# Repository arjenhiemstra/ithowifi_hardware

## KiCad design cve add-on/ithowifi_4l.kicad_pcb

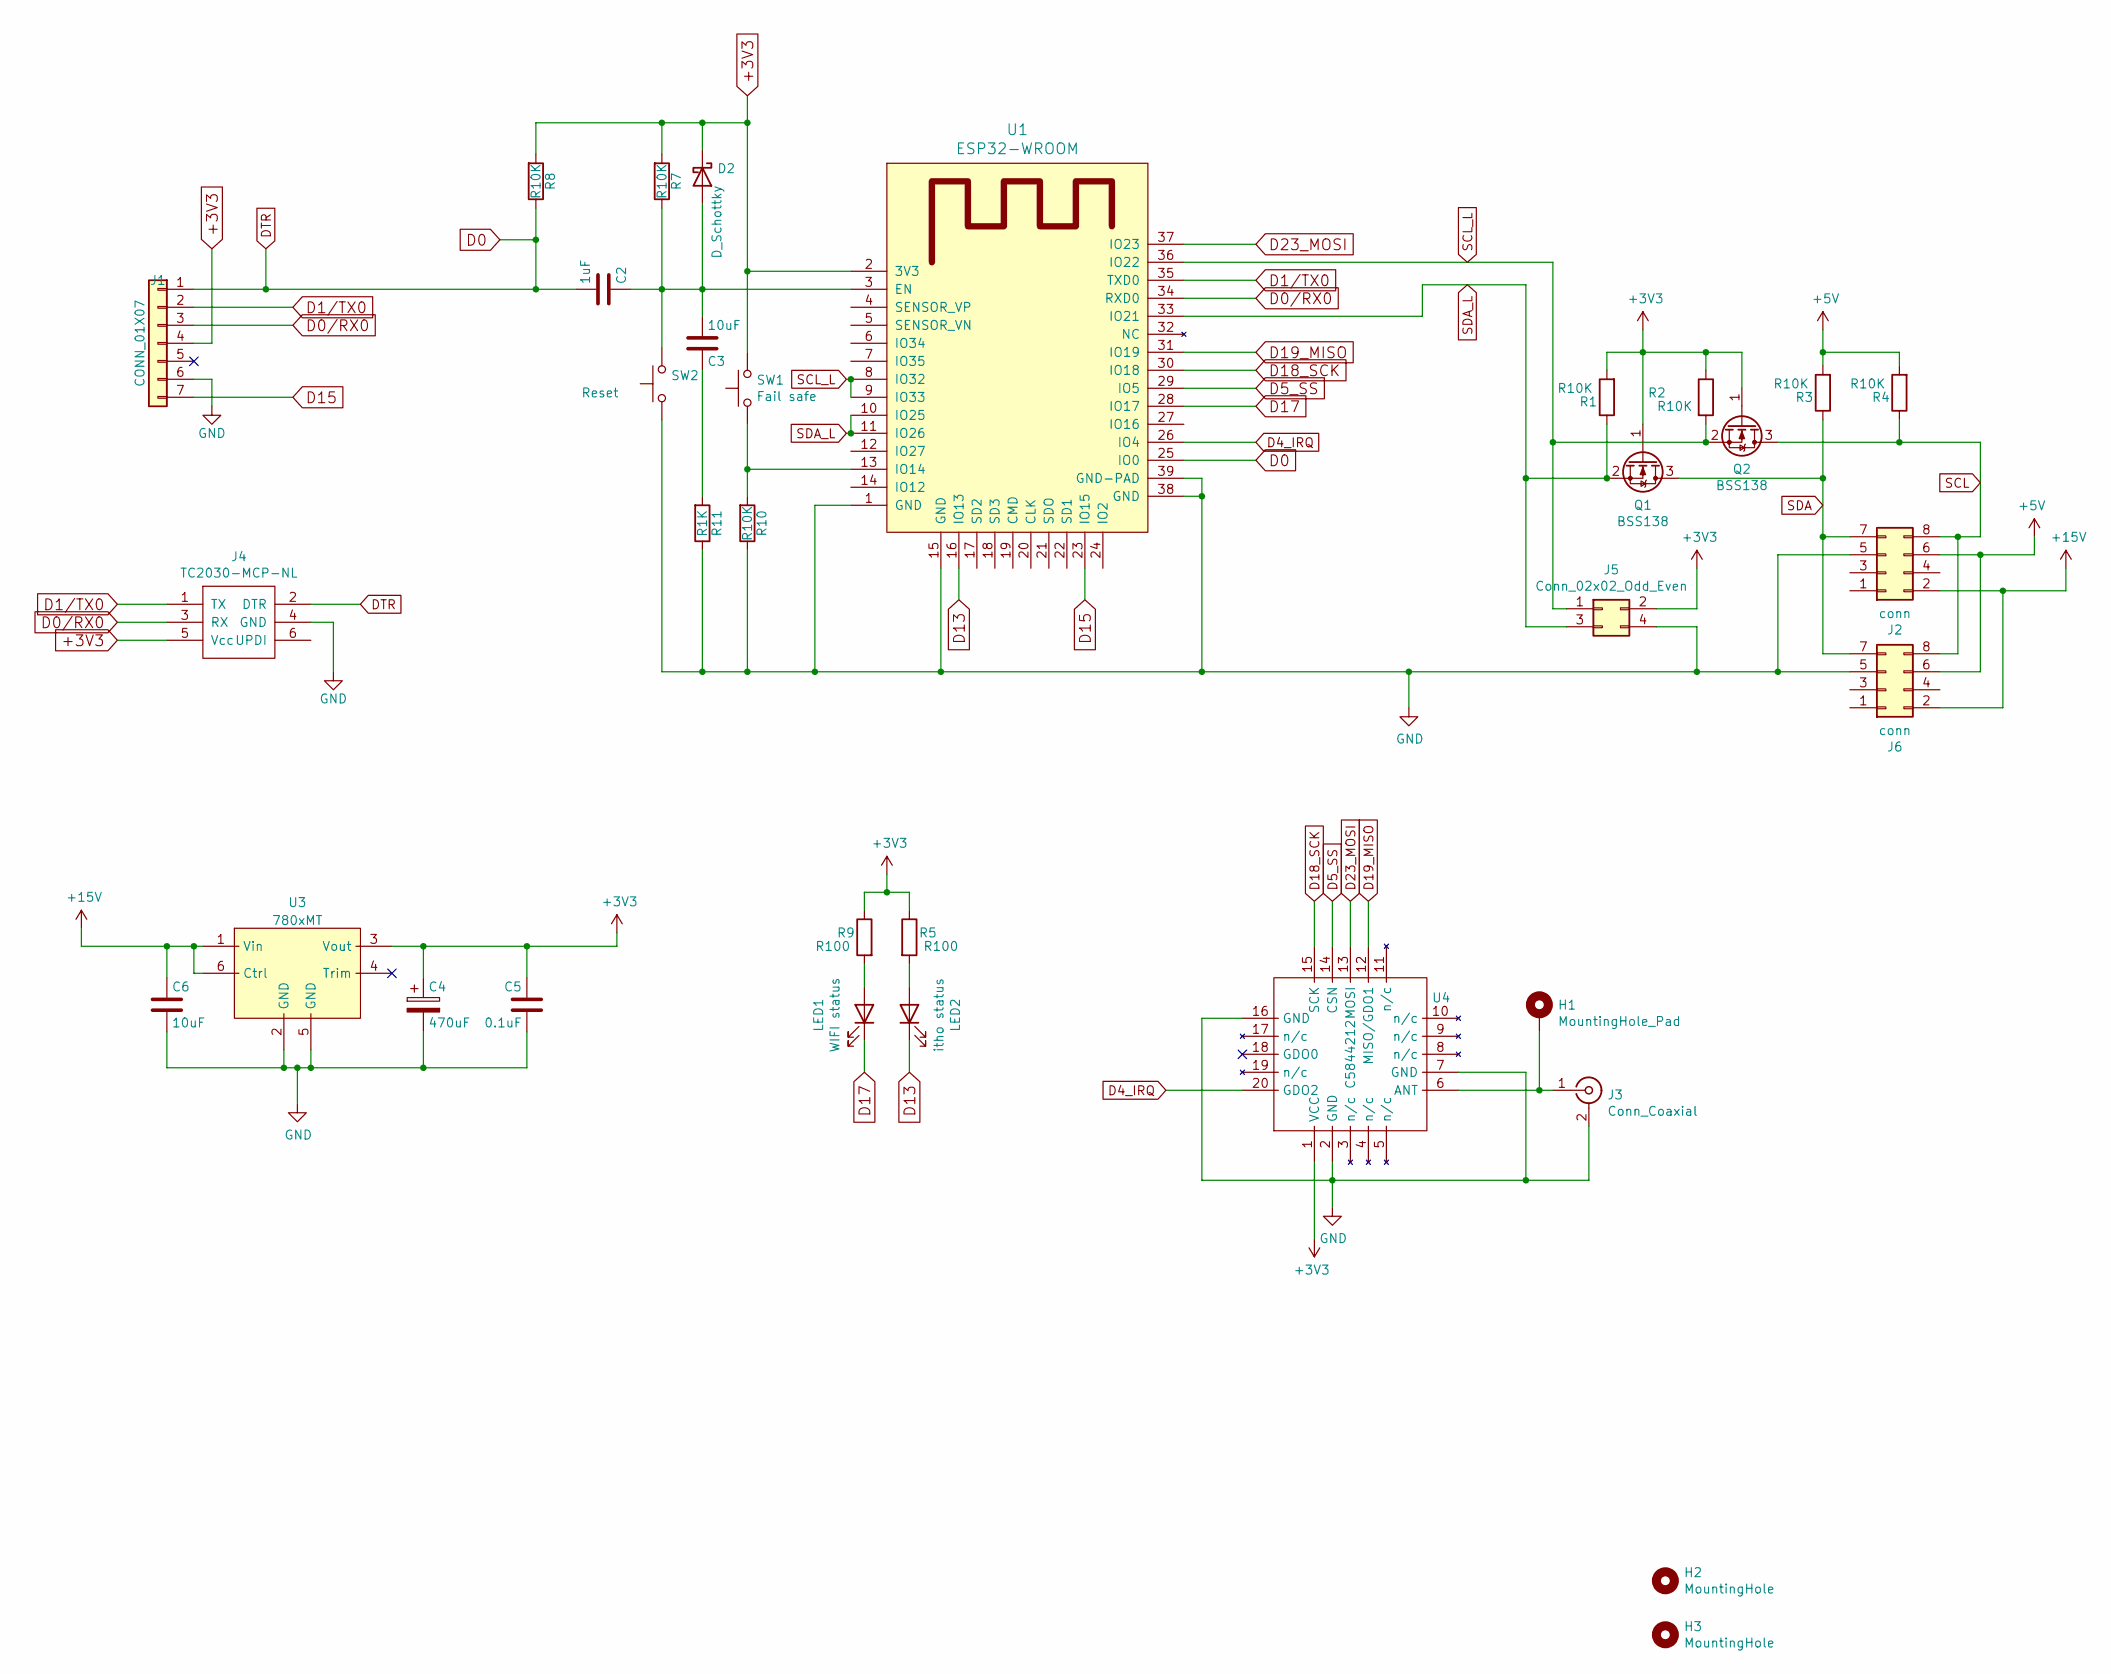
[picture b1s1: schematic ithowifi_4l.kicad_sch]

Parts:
C2: 1uF; C_0805_2012Metric; LCSC C28323
C3: 10uF; C_0805_2012Metric; LCSC C28323
C4: 470uF; CP_EIA-7343-31_Kemet-D; LCSC C7229
C5: 0.1uF; C_0805_2012Metric; LCSC C49678
C6: 10uF; C_0805_2012Metric; LCSC C110053
D2: D_Schottky; D_SOD-123
H1: MountingHole_Pad; Pin_D1.0mm_L10.0mm
H2, H3: MountingHole; MountingHole_2.5mm
J1: CONN_01X07; PinHeader_1x07_P2.54mm_Vertical
J2: conn; PM254-2-04-S-8.5; LCSC C3975149
J3: Conn_Coaxial; SMA_Amphenol_132289_EdgeMount
J4: TC2030-MCP-NL; TC2020-MCP-NL
J5: Conn_02x02_Odd_Even; PinHeader_2x02_P2.54mm_Vertical_SMD
J6: conn; PinHeader_2x04_P2.54mm_Vertical_SMD; LCSC C3294462
LED1: WIFI status; LED_0805_2012Metric; LCSC C2293
LED2: itho status; LED_0805_2012Metric; LCSC C2293
Q1, Q2: BSS138; SOT-23W; LCSC C170166
R1, R2, R3, R4, R7, R8, R10: R10K; R_0805_2012Metric; LCSC C17414
R5, R9: R100; R_0805_2012Metric; LCSC C17408
R11: R1K; R_0805_2012Metric; LCSC C17414
SW1: Fail safe; TS-1187; LCSC C92589
SW2: Reset; TS-1187; LCSC C92589
U1: ESP32-WROOM; ESP32-WROOM-32E; LCSC C473012
U3: 780xMT; Mornsun 780xMT
U4: E70-433MT14S; LCSC C5844212

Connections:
+3V3: C4.1, C5.1, D2.1 (K), J1.4, J4.5 (Vcc), J5.2, Q1.1 (G), Q2.1 (G), R1.2, R2.1, R5.1, R7.2, R8.2, R9.1, SW1.2, U1.2 (3V3), U3.3 (Vout), U4.1 (VCC); also elsewhere on the board
+5V: J2.6, J6.6, R3.2, R4.2
+15V: C6.1, J2.2, J6.2, U3.1 (Vin), U3.6 (Ctrl)
D0: C2.2, J1.1, J4.2 (DTR), R8.1, U1.25 (IO0)
D0/RX0: J1.3, J4.3 (RX), U1.34 (RXD0)
D1/TX0: J1.2, J4.1 (TX), U1.35 (TXD0)
D4_IRQ: U1.26 (IO4), U4.20 (GDO2)
D5_SS: U1.29 (IO5), U4.14 (CSN)
D13: LED2.1 (K), U1.16 (IO13)
D15: J1.7, U1.23 (IO15)
D17: LED1.1 (K), U1.28 (IO17)
D18_SCK: U1.30 (IO18), U4.15 (SCK)
D19_MISO: U1.31 (IO19), U4.12 (MISO/GDO1)
D23_MOSI: U1.37 (IO23), U4.13 (MOSI)
GND: C4.2, C5.2, C6.2, J1.6, J2.5, J3.2 (Ext), J4.4 (GND), J5.4, J6.5, R10.1, R11.1, SW2.1, U1.1 (GND), U1.15 (GND), U1.38 (GND), U1.39 (GND-PAD), U3.2 (GND), U3.5 (GND), U4.2 (GND), U4.7 (GND), U4.16 (GND); also elsewhere on the board
unnamed: C3.1, R11.2
unnamed: C2.1, C3.2, D2.2 (A), R7.1, SW2.2, U1.3 (EN)
unnamed: H1.1, J3.1 (In), U4.6 (ANT)
unnamed: LED1.2 (A), R9.2
unnamed: LED2.2 (A), R5.2
unnamed: R10.2, SW1.1, U1.13 (IO14)
SCL: J2.8, J6.8, Q2.3 (D), R4.1
SCL_L: J5.1, Q2.2 (S), R2.2, U1.8 (IO32), U1.9 (IO33), U1.36 (IO22); also elsewhere on the board
SDA: J2.7, J6.7, Q1.3 (D), R3.1
SDA_L: J5.3, Q1.2 (S), R1.1, U1.10 (IO25), U1.11 (IO26), U1.33 (IO21); also elsewhere on the board

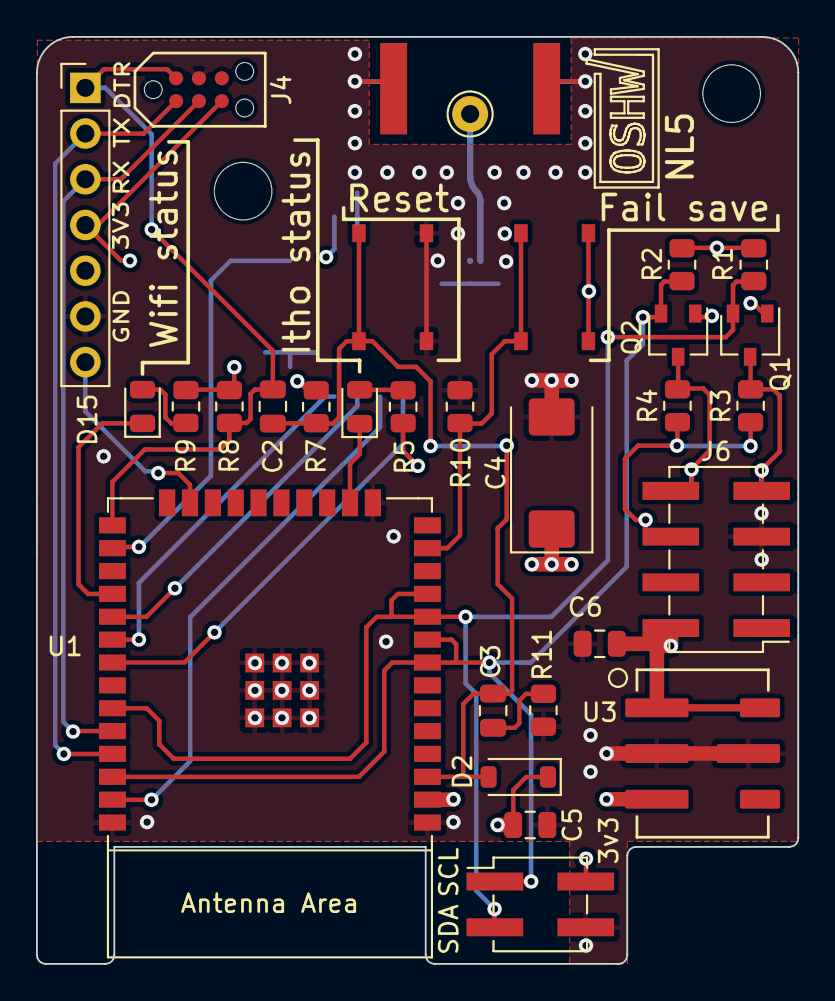
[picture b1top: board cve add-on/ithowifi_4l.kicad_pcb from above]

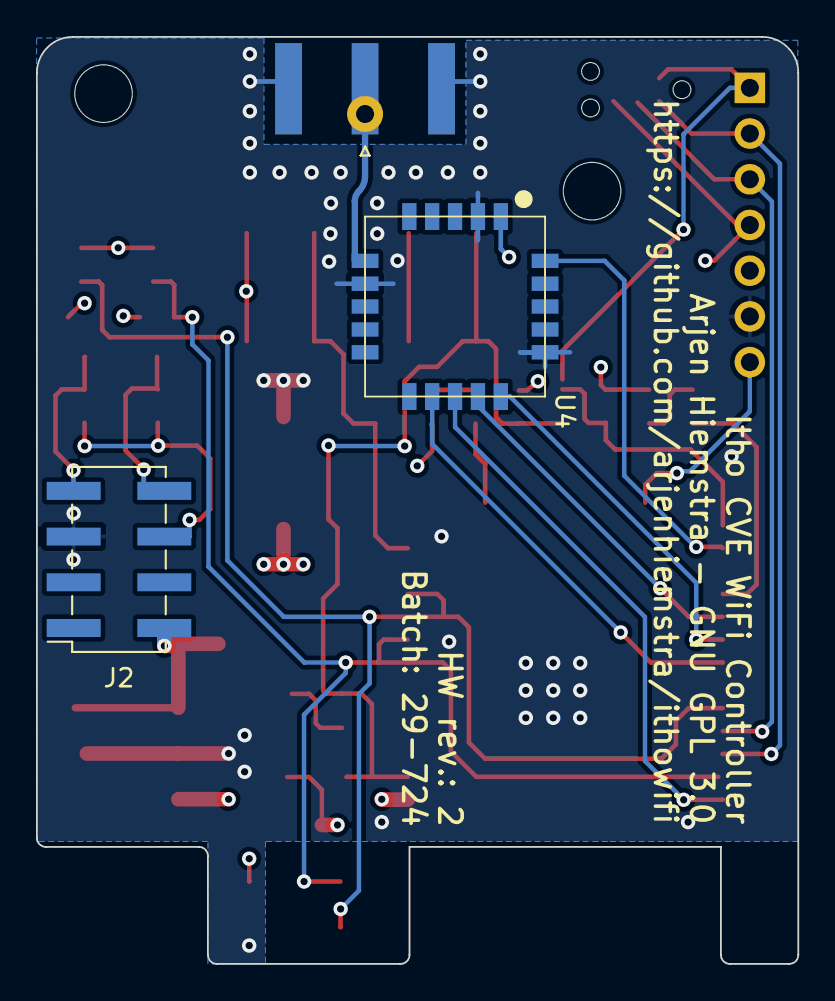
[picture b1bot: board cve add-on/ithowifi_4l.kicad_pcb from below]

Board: 4 copper layers, 42.3 x 51.5 mm, 34 parts (3 on the bottom side), 25 nets.

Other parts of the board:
Je: Conn_02x02_Odd_Even; PinHeader_2x02_P2.54mm_Vertical_SMD

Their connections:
+3V3: Je.2; also elsewhere on the board
GND: Je.4; also elsewhere on the board
SCL_L: Je.1; also elsewhere on the board
SDA_L: Je.3; also elsewhere on the board

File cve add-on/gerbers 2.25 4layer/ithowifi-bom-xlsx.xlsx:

Comment | Designator | Footprint | LCSC Part Number
LED Red | LED1,LED2 | LED_0805 | C84256
R100 | R9,R5 | 0805 | C17408
10uF | C3, C6 | 0805 | C15850
470uF | C4 | CP_EIA-7343-31_Kemet-D | C7229
ESP32-WROOM-32E | U1 | SMD-38_EP_18.0x25.5x1.27P | C82899 | C701341
B5819W | D2 | SOD-123 | C8598
0,1uF | C5 | 0805 | C49678
1uF | C2 | 0805 | C28323
R10K | R10,R8,R7,R4,R3,R2,R1 | 0805 | C17414
BSS138 | Q2,Q1 | SOT-23-3 | C78284
SW_SPST | SW1,SW2 | SMD-SW-4_5.1X5.1X1.5 | C318884
R1K | R11 | 0805 | C17513
K7803MT-500R4 | U3 | DFN | C2692188 | C2692194
E07-900MM10S | U4 | 10x10mm | C5844212
PinSocket_2x04_P2.54mm_Vertical | J2 | Plugin,P=2.54mm | C358726

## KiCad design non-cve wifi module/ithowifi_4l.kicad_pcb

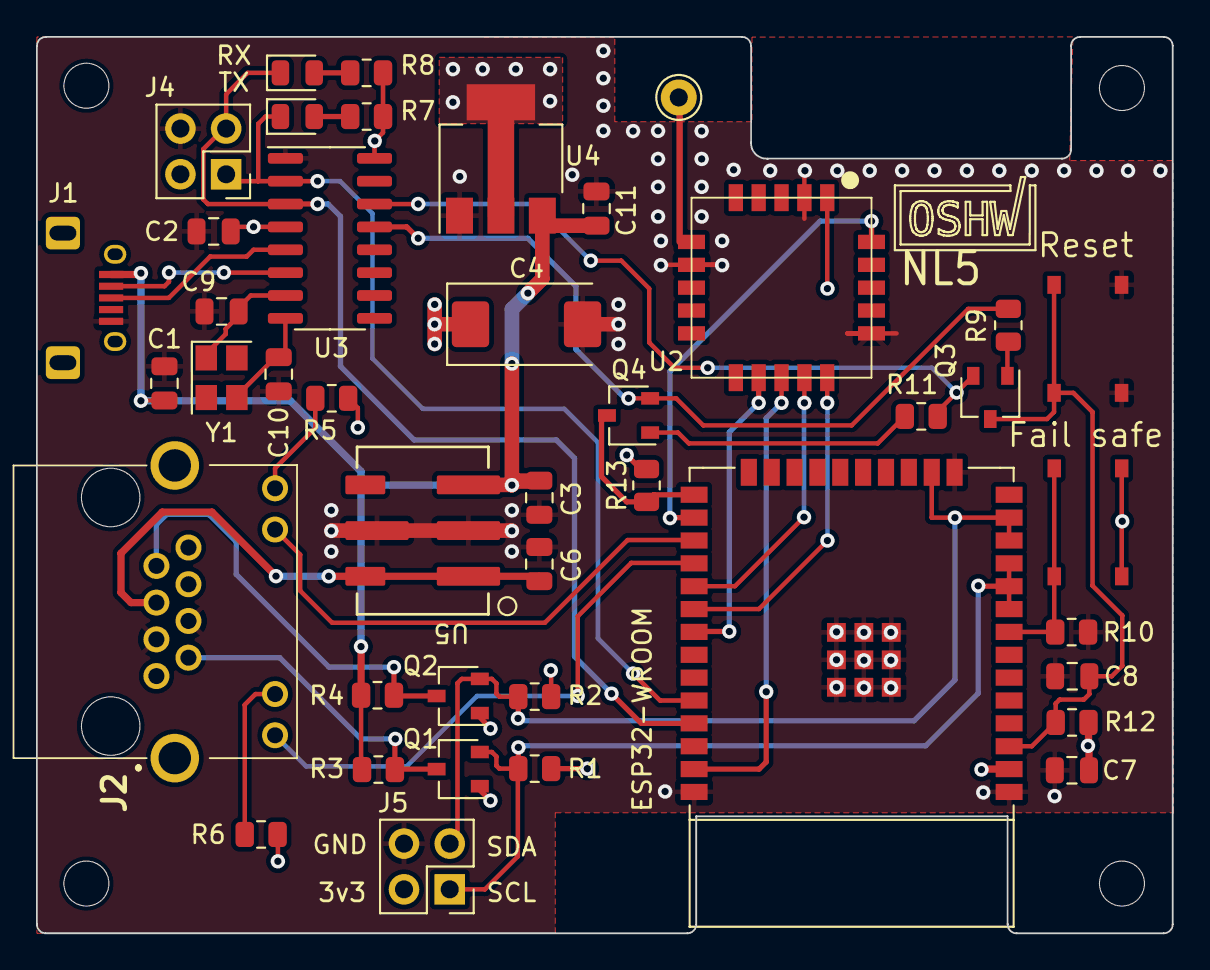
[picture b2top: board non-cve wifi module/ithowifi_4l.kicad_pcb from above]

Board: 4 copper layers, 63.1 x 49.8 mm, 46 parts (0 on the bottom side), 33 nets.

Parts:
C1, C2, C7: 0.1uF; C_0805_2012Metric
C3: 22uF; C_0805_2012Metric
C4: 470uF; CP_EIA-7343-31_Kemet-D
C6, C8, C11: 10uF; C_0805_2012Metric
C9, C10: 33pF; C_0805_2012Metric
H1, H2, H3, H4: MountingHole; MountingHole_2.5mm
H5: MountingHole_Pad; Pin_D1.0mm_L10.0mm
J1: USB_B_Micro; micro usb
J2: RJ45_LED_Shielded; RRJ45R08PC000
J4, J5: Conn_02x02_Odd_Even; PinHeader_2x02_P2.54mm_Vertical
LED1: TX; LED_0805_2012Metric
LED2: RX; LED_0805_2012Metric
Q1, Q2: BSS138; SOT-23W
Q3, Q4: BC847; SOT-23W
R1, R2, R3, R4, R9, R10, R11, R12, R13: R10K; R_0805_2012Metric
R5, R6: R100; R_0805_2012Metric
R7, R8: R1K; R_0805_2012Metric
SW1: Fail safe; TS-1187
SW2: Reset; TS-1187
U1: ESP32-WROOM; ESP32-WROOM-32E
U2: E70-433MT14S
U3: CH340G; SOIC-16_3.9x9.9mm_P1.27mm
U4: AMS1117-3.3; SOT-223-3_TabPin2
U5: 780xMT; Mornsun 780xMT
Y1: Crystal_GND24_Small; Crystal_SMD_TXC_7M-4Pin_3.2x2.5mm

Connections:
+3V3: C2.1, C4.1, C7.1, J4.2, J5.2, Q1.1 (G), Q2.1 (G), R1.2, R2.2, R5.1, R6.1, R7.1, R8.1, R12.2, R13.2, SW1.2, U1.2 (3V3), U2.1 (VCC), U3.4 (V3), U3.16 (VCC), U4.2 (VO)
+5V: C1.1, C3.1, C11.1, J1.1 (VBUS), R3.2, R4.2, U4.3 (VI), U5.3 (Vout)
+15V: C6.1, J2.5, U5.1 (Vin), U5.6 (Ctrl)
D0: Q4.3 (C), R13.1, U1.25 (IO0)
D0/RX0: J4.1, LED1.1 (K), U1.34 (RXD0), U3.2 (TXD)
D1/TX0: J4.3, LED2.1 (K), U1.35 (TXD0), U3.3 (RXD)
D4_IRQ: U1.26 (IO4), U2.20 (GDO2)
D5_SS: U1.29 (IO5), U2.14 (CSN)
D16_SYS_STATUS: J2.11, U1.27 (IO16)
D17_WIFI_STATUS: J2.9, U1.28 (IO17)
D18_SCK: U1.30 (IO18), U2.15 (SCK)
D19_MISO: U1.31 (IO19), U2.12 (MISO/GDO1)
D23_MOSI: U1.37 (IO23), U2.13 (MOSI)
DTR: Q4.2 (E), R9.1, U3.13 (~DTR)
EN: C8.2, Q3.3 (C), R12.1, SW2.2, U1.3 (EN)
GND: C1.2, C2.2, C3.2, C4.2, C6.2, C7.2, C8.1, C9.2, C10.2, C11.2, J1.5 (GND), J2.3, J2.4, J4.4, J5.4, R10.1, SW2.1, U1.1 (GND), U1.15 (GND), U1.38 (GND), U1.39 (GND-PAD), U2.2 (GND), U2.7 (GND), U2.16 (GND), U3.1 (GND), U4.1 (GND), U5.2 (GND), U5.5 (GND)
unnamed: J1.3 (D+), U3.5 (UD+)
unnamed: J1.2 (D-), U3.6 (UD-)
unnamed: J2.10, R6.2
unnamed: J2.12, R5.2
unnamed: LED1.2 (A), R7.2
unnamed: LED2.2 (A), R8.2
unnamed: J2.2, Q1.3 (D), R3.1
unnamed: J2.7, Q2.3 (D), R4.1
unnamed: Q3.1 (B), R9.2
unnamed: Q4.1 (B), R11.2
unnamed: R10.2, SW1.1, U1.8 (IO32)
unnamed: H5.1, U2.6 (ANT)
unnamed: C9.1, U3.7 (XI), Y1.1
unnamed: C10.1, U3.8 (XO), Y1.3
RTS: Q3.2 (E), R11.1, U3.14 (~RTS)
SCL_L: J5.1, Q1.2 (S), R1.1, U1.9 (IO33), U1.10 (IO25), U1.11 (IO26)
SDA_L: J5.3, Q2.2 (S), R2.1, U1.12 (IO27), U1.13 (IO14), U1.16 (IO13)

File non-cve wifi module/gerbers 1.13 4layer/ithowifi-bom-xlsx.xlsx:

Comment | Designator | Footprint | LCSC Part Number
10uF | C6,C8,C11 | C_0805_2012Metric | C15850
USB_B_Micro | J1 | MICRO-USB-SMD | C381143
R10K | R9,R13,R12,R11,R10,R4,R3,R2,R1 | R_0805_2012Metric | C17414
R1K | R8,R7 | R_0805_2012Metric | C17513
R100 | R6,R5 | R_0805_2012Metric | C17408
0.1uF | C2,C1,C7 | C_0805_2012Metric | C49678
AMS1117-3.3 | U4 | SOT-223-3_TabPin2 | C6186
CH340C | U3 | SOIC-16_3.9x9.9mm_P1.27mm | C84681
BC847 | Q4,Q3 | SOT-23 | C6749
RJ45_LED_Shielded | J2 | RRJ45R08PC000 | C386757
Fail safe | SW1 | SMD-SW-4_5.1X5.1X1.5 | C318884
470uF | C4 | CP_EIA-7343-31_Kemet-D | C7229
ESP32-WROOM | U1 | ESP32-WROOM-32 | C82899
TX | LED1 | LED_0805_2012Metric | C84256
RX | LED2 | LED_0805_2012Metric | C84256
BSS138 | Q2,Q1 | SOT-23 | C78284
Reset | SW2 | SMD-SW-4_5.1X5.1X1.5 | C318884
K7805MT-500R4 | U5 | DFN | C2684892
22uF | C3 | C_0805_2012Metric | C45783
E07-900MM10S | U2 | 10x10mm | C5844212

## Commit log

2024-02-24 intial commit

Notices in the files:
cve add-on/ithowifi_4l.kicad_pcb:
Arjen Hiemstra - GNU GPL 3.0
